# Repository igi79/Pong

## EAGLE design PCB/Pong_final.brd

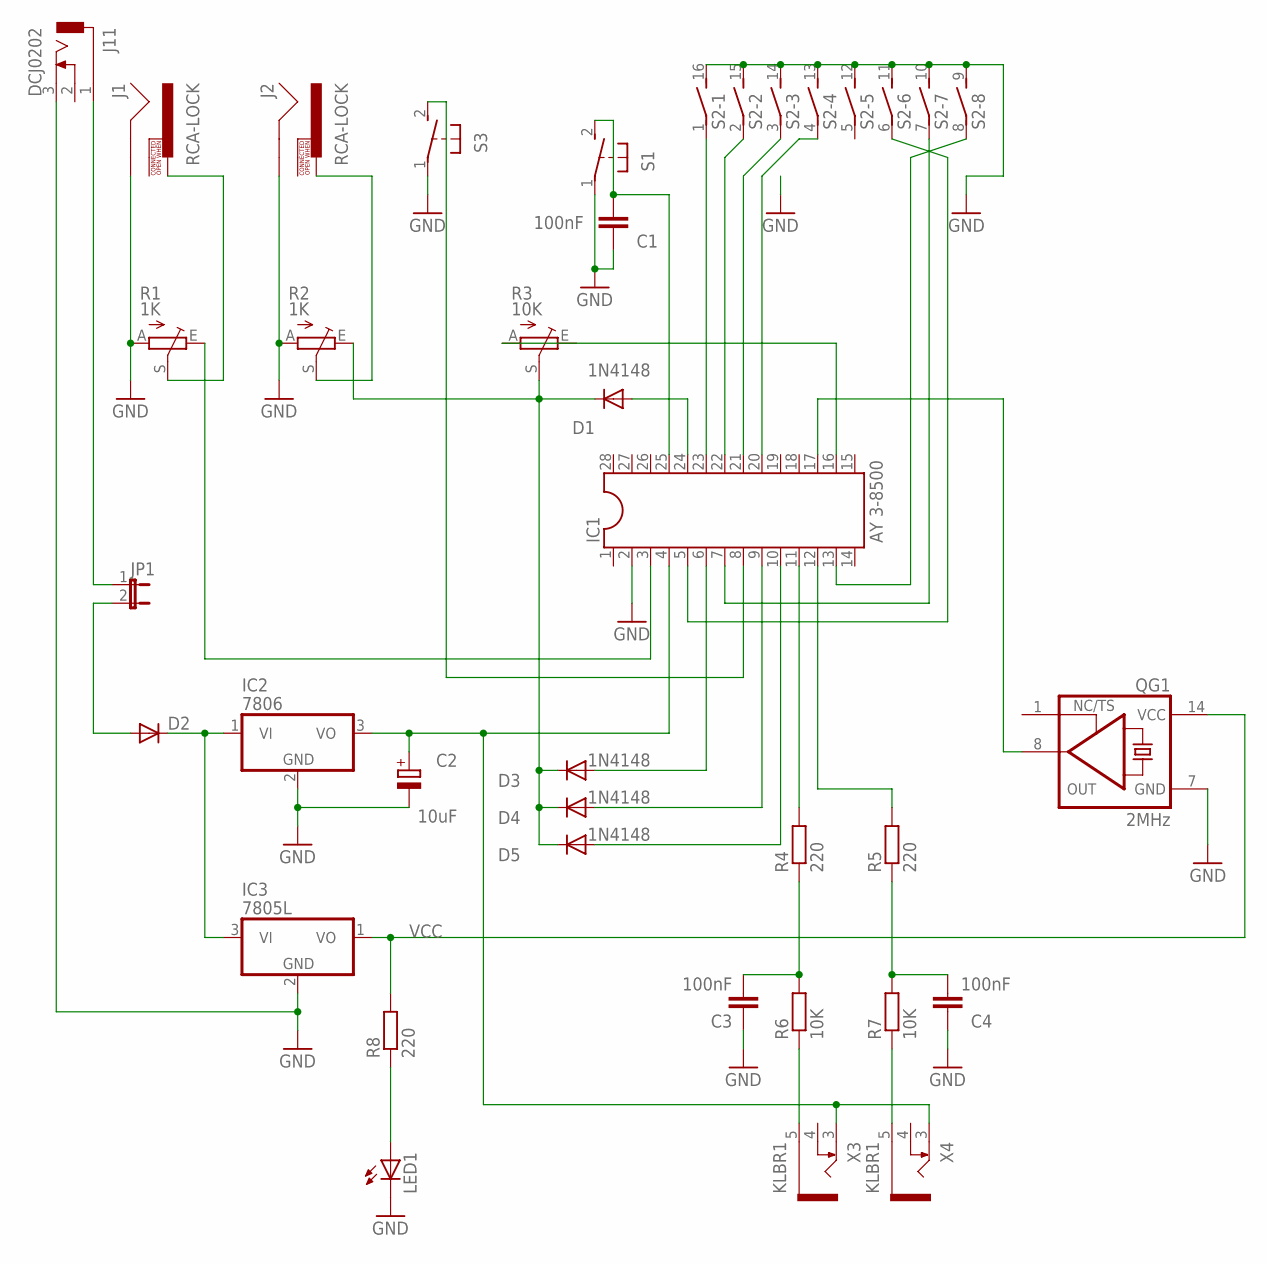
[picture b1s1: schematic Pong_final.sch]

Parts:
C1: 100nF; C0805
C2: 10uF; E2,5-6
C3, C4: 100nF; C0805K
D1, D3, D4, D5: 1N4148; MINIMELF
D2: DIODE-MELF-MLL41; MELF-MLL41
IC1: AY 3-8500; DIL28-6
IC2: 7806; TO220V
IC3: 7805L; TO92
J1, J2: RCA-LOCK; RCA_LOCK
J11: DCJ0202
JP1: JP1E; JP1
LED1: LEDB155; Q62902-B155
QG1: 2MHz; DIL14S
R1, R2: 1K; CA6V
R3: 10K; CA6V
R4, R5, R8: 220; R0805
R6, R7: 10K; R0805
S1, S3: 31-XX; B3F-31XX
S2: DIP08S
X3, X4: KLBR1

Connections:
GND: C1.1, C2.-, C3.1, C4.1, IC1.2, IC2.2 (GND), IC3.2 (GND), J1.SHELL, J2.SHELL, J11.3, LED1.K (C), QG1.7 (GND), R1.A, R2.A, S1.1, S2.9 (2), S2.10 (2), S2.11 (2), S2.12 (2), S2.13 (2), S2.14 (2), S2.15 (2), S2.16 (2), S3.1
unnamed: D2.C, IC2.1 (VI), IC3.3 (VI)
unnamed: D2.A, JP1.2
unnamed: LED1.A, R8.1
unnamed: J1.PIN, R1.S
unnamed: R6.1, X3.5
unnamed: IC1.3, R1.E
unnamed: J2.PIN, R2.S
unnamed: IC1.17, QG1.8 (OUT)
unnamed: IC1.5, S2.6 (1)
unnamed: IC1.7, S2.7 (1)
unnamed: IC1.13, S2.8 (1)
unnamed: D3.A, IC1.6
unnamed: D4.A, IC1.9
unnamed: D5.A, IC1.10
unnamed: C2.+, IC1.4, IC2.3 (VO), X3.3, X4.3
unnamed: IC1.11, R4.2
unnamed: IC1.12, R5.2
unnamed: D1.A, IC1.24
unnamed: IC1.16, R3.A
unnamed: IC1.8, S3.2 (S)
unnamed: IC1.23, S2.1
unnamed: IC1.22, S2.2 (1)
unnamed: IC1.21, S2.3 (1)
unnamed: IC1.20, S2.4 (1)
unnamed: J11.1, JP1.1
unnamed: C1.2, IC1.25, S1.2 (S)
unnamed: D1.C, D3.C, D4.C, D5.C, R2.E, R3.S
unnamed: R7.1, X4.5
unnamed: C3.2, R4.1, R6.2
unnamed: C4.2, R5.1, R7.2
VCC: IC3.1 (VO), QG1.14 (VCC), R8.2

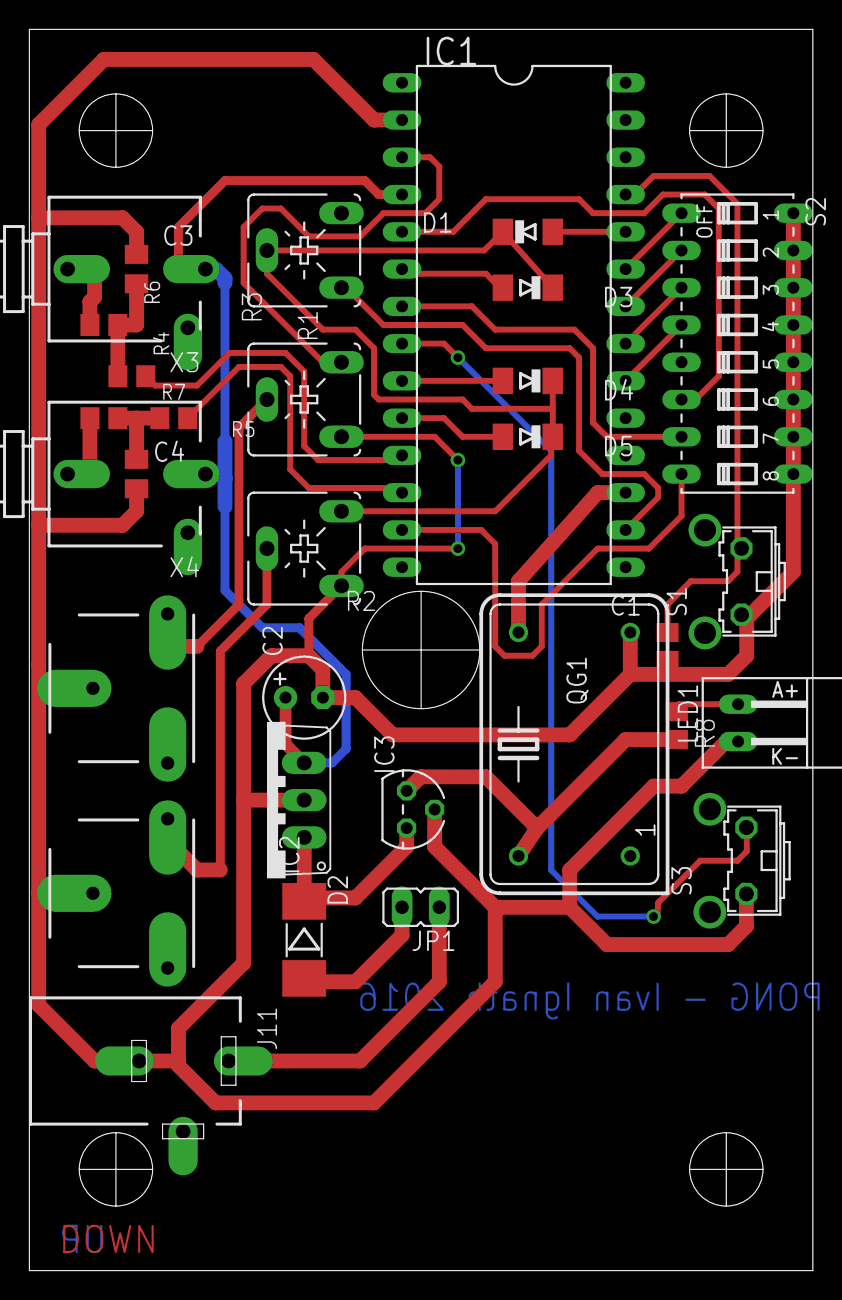
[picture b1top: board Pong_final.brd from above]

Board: 2 copper layers, 53.4 x 84.6 mm, 31 parts (0 on the bottom side), 32 nets.

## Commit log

2016-03-12 PCB img

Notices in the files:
parts and their libraries:
SparkFun-Connectors: Licensing: Creative Commons ShareAlike 4.0 International - https://creativecommons.org/licenses/by-sa/4.0
